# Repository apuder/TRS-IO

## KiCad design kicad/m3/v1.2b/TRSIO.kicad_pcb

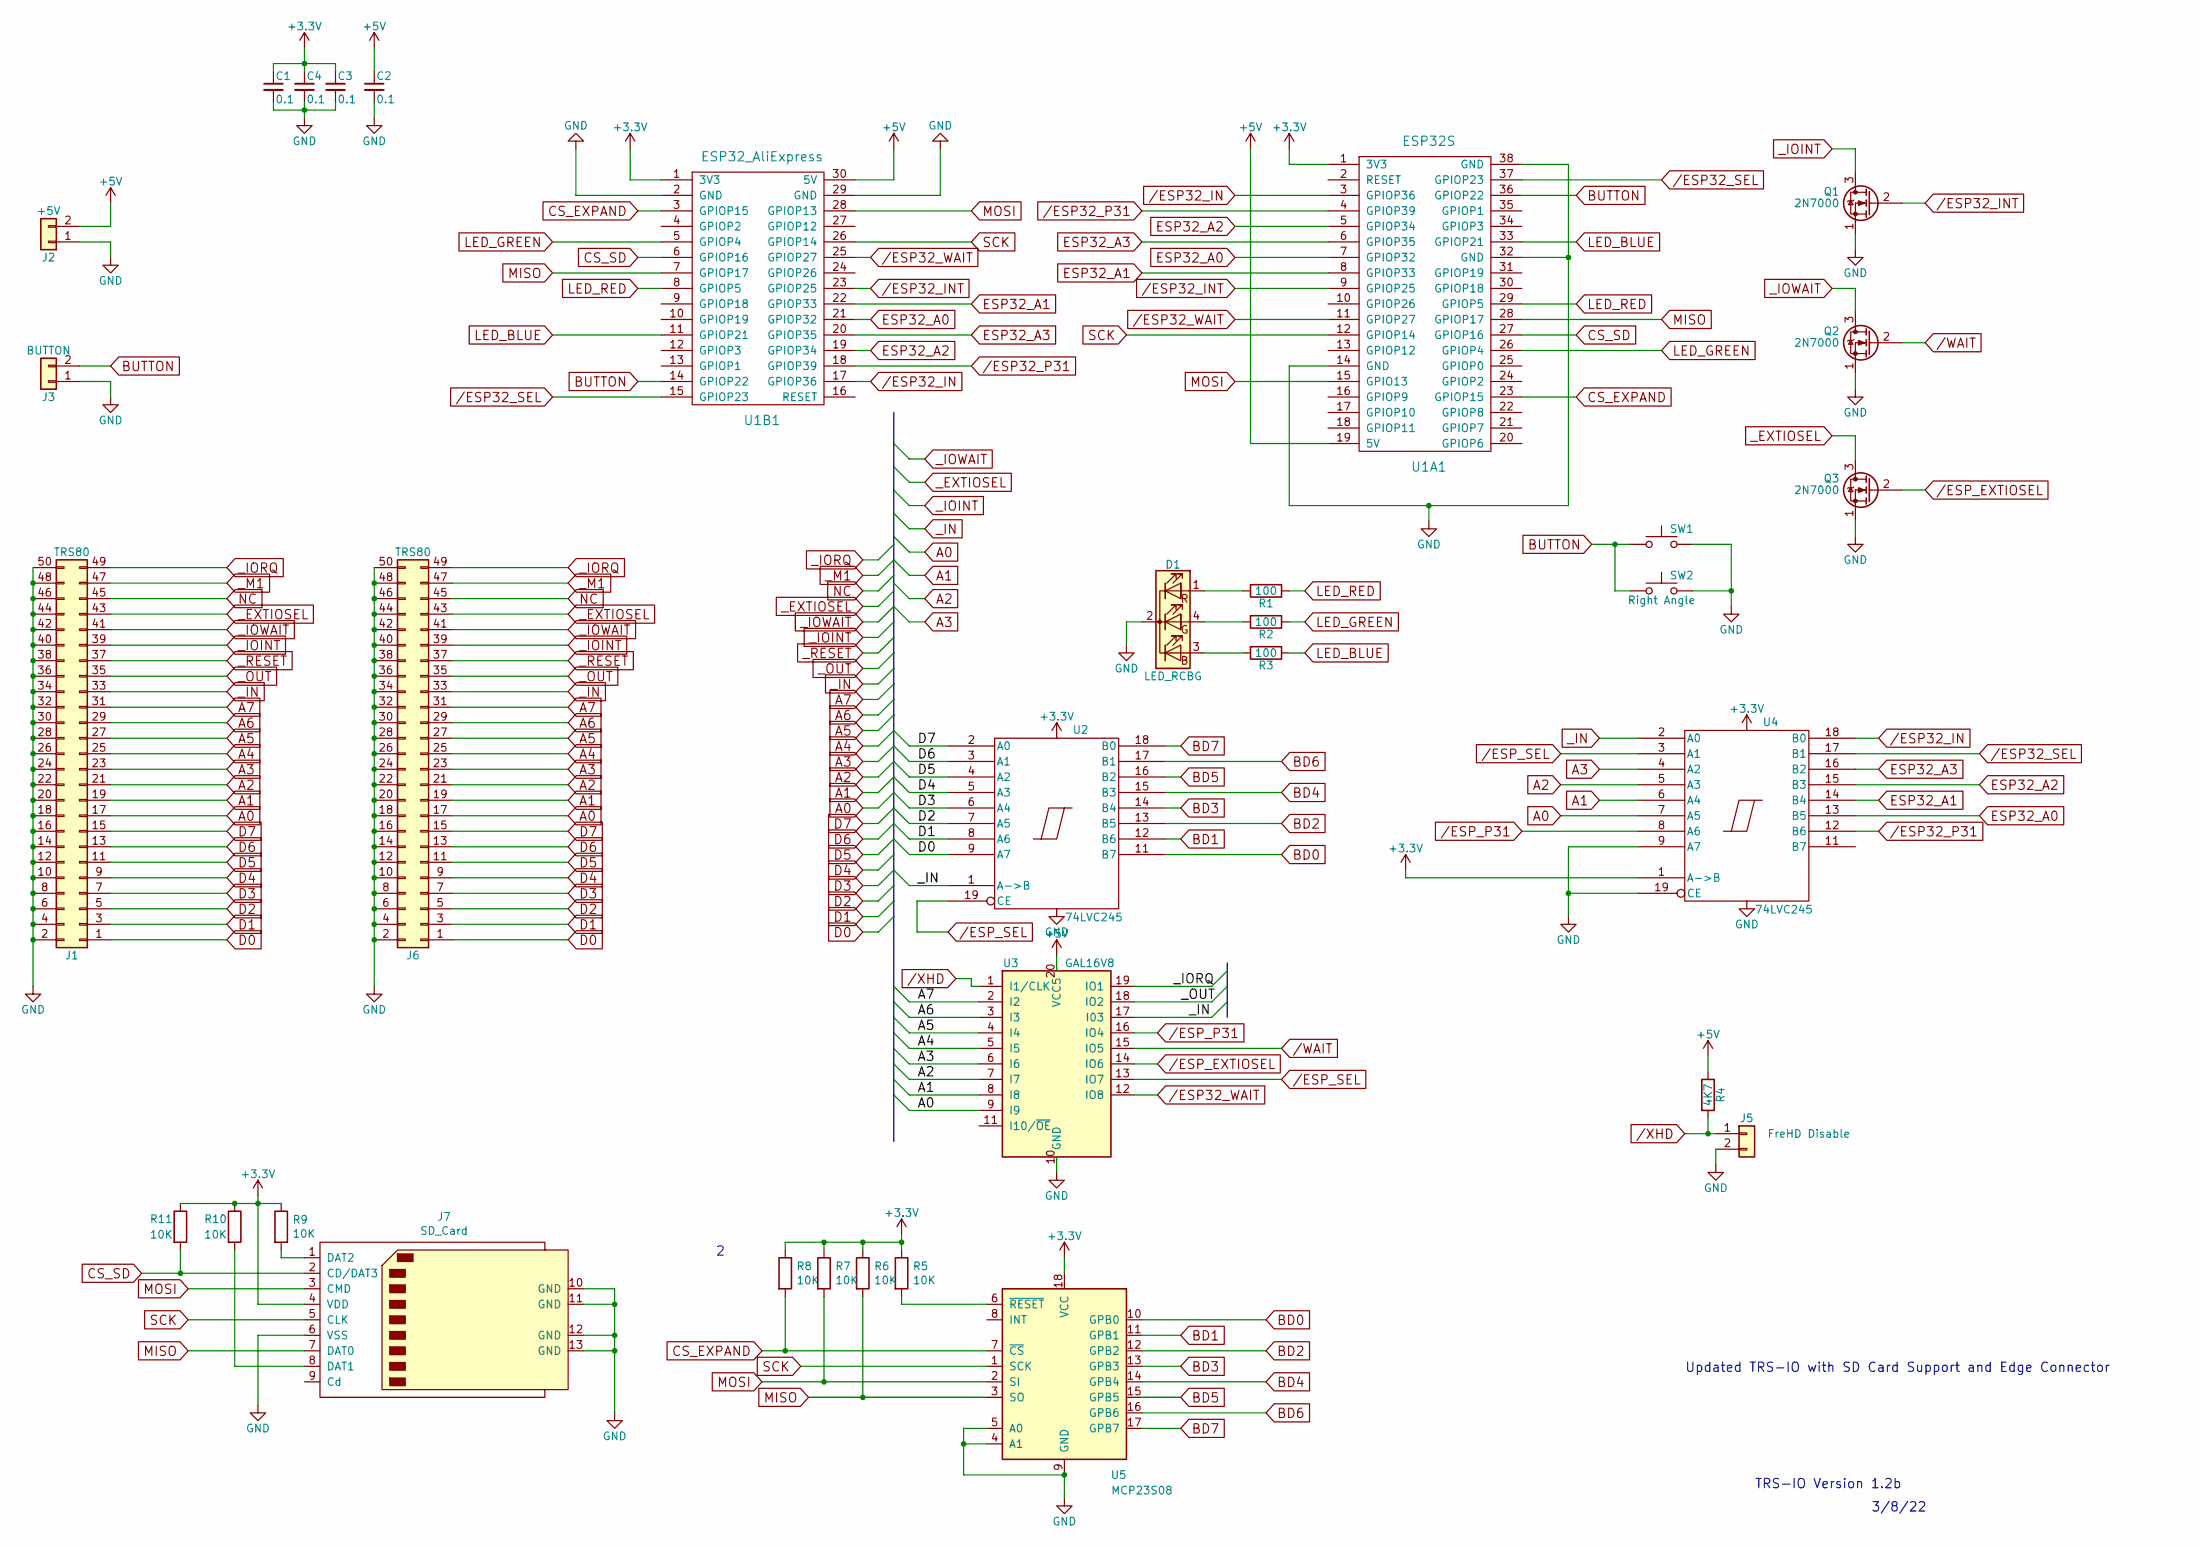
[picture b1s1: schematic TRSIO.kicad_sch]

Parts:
C1, C2, C3, C4: 0.1; C_Disc_D3.0mm_W2.0mm_P2.50mm
D1: LED_RCBG; LED_D5.0mm-4
J1: TRS80; Pin_Header_Straight_2x25_Pitch2.54mm
J2: +5V; Pin_Header_Straight_1x02_Pitch2.54mm
J3: BUTTON; Pin_Header_Straight_1x02_Pitch2.54mm
J5: FreHD Disable; Pin_Header_Straight_1x02_Pitch2.54mm
J6: TRS80; EDGE50
J7: SD_Card; TFP09-2-12B
Q1, Q2, Q3: 2N7000; TO-92_Molded_Narrow
R1, R2, R3: 100; R_Axial_DIN0207_L6.3mm_D2.5mm_P7.62mm_Horizontal
R4: 4K7; R_Axial_DIN0207_L6.3mm_D2.5mm_P7.62mm_Horizontal
R5, R6, R7, R8, R9, R10, R11: 10K; R_Axial_DIN0207_L6.3mm_D2.5mm_P7.62mm_Horizontal
SW1: SW_Push; SW_PUSH_6mm_h9.5mm
SW2: Right Angle; SW_Tactile_SPST_Angled_PTS645Vx31-2LFS
U1A1: ESP32S; DIP-38_W22.9mm
U1B1: ESP32_AliExpress; DIP-30_W25.4mm
U2, U4: 74LVC245; DIP-20_W7.62mm
U3: GAL16V8; DIP-20_W7.62mm
U5: MCP23S08; DIP-18_W7.62mm

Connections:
+3V3: C1.1, C3.1, C4.1, J7.4 (VDD), R5.1, R6.1, R7.1, R8.1, R9.1, R10.1, R11.1, U1A1.1 (3V3), U1B1.1 (3V3), U2.20 (VCC), U4.1 (A->B), U4.20 (VCC), U5.18 (VCC)
+5V: C2.1, J2.2, R4.1, U1A1.19 (5V), U1B1.30 (5V), U3.20 (VCC5)
A0: J1.17, J6.17, U3.9 (I9), U4.7 (A5)
A1: J1.19, J6.19, U3.8 (I8), U4.6 (A4)
A2: J1.21, J6.21, U3.7 (I7), U4.5 (A3)
A3: J1.23, J6.23, U3.6 (I6), U4.4 (A2)
A4: J1.25, J6.25, U3.5 (I5)
A5: J1.27, J6.27, U3.4 (I4)
A6: J1.29, J6.29, U3.3 (I3)
A7: J1.31, J6.31, U3.2 (I2)
BD0: U2.11 (B7), U5.10 (GPB0)
BD1: U2.12 (B6), U5.11 (GPB1)
BD2: U2.13 (B5), U5.12 (GPB2)
BD3: U2.14 (B4), U5.13 (GPB3)
BD4: U2.15 (B3), U5.14 (GPB4)
BD5: U2.16 (B2), U5.15 (GPB5)
BD6: U2.17 (B1), U5.16 (GPB6)
BD7: U2.18 (B0), U5.17 (GPB7)
BUTTON: J3.2, SW1.1, SW2.1, U1A1.36 (GPIOP22), U1B1.14 (GPIOP22)
CS_EXPAND: R8.2, U1A1.23 (GPIOP15), U1B1.3 (GPIOP15), U5.7 (~CS)
CS_SD: J7.2 (CD/DAT3), R11.2, U1A1.27 (GPIOP16), U1B1.6 (GPIOP16)
D0: J1.1, J6.1, U2.9 (A7)
D1: J1.3, J6.3, U2.8 (A6)
D2: J1.5, J6.5, U2.7 (A5)
D3: J1.7, J6.7, U2.6 (A4)
D4: J1.9, J6.9, U2.5 (A3)
D5: J1.11, J6.11, U2.4 (A2)
D6: J1.13, J6.13, U2.3 (A1)
D7: J1.15, J6.15, U2.2 (A0)
ESP32_A0: U1A1.7 (GPIOP32), U1B1.21 (GPIOP32), U4.13 (B5)
ESP32_A1: U1A1.8 (GPIOP33), U1B1.22 (GPIOP33), U4.14 (B4)
ESP32_A2: U1A1.5 (GPIOP34), U1B1.19 (GPIOP34), U4.15 (B3)
ESP32_A3: U1A1.6 (GPIOP35), U1B1.20 (GPIOP35), U4.16 (B2)
GND: C1.2, C2.2, C3.2, C4.2, D1.2 (K), J1.2, J1.4, J1.6, J1.8, J1.10, J1.12, J1.14, J1.16, J1.18, J1.20, J1.22, J1.24, J1.26, J1.28, J1.30, J1.32, J1.34, J1.36, J1.38, J1.40, J1.42, J1.44, J1.46, J1.48, J1.50, J2.1, J3.1, J5.2, J6.2, J6.4, J6.6, J6.8, J6.10, J6.12, J6.14, J6.16, J6.18, J6.20, J6.22, J6.24, J6.26, J6.28, J6.30, J6.32, J6.34, J6.36, J6.38, J6.40, J6.42, J6.44, J6.46, J6.48, J6.50, J7.6 (VSS), J7.10 (GND), J7.11 (GND), J7.12 (GND), J7.13 (GND), Q1.1 (S), Q2.1 (S), Q3.1 (S), SW1.2, SW2.2, U1A1.14 (GND), U1A1.32 (GND), U1A1.38 (GND), U1B1.2 (GND), U1B1.29 (GND), U2.10 (GND), U3.10 (GND), U4.9 (A7), U4.10 (GND), U4.19 (CE), U5.4 (A1), U5.5 (A0), U5.9 (GND)
LED_BLUE: R3.1, U1A1.33 (GPIOP21), U1B1.11 (GPIOP21)
LED_GREEN: R2.1, U1A1.26 (GPIOP4), U1B1.5 (GPIOP4)
LED_RED: R1.1, U1A1.29 (GPIOP5), U1B1.8 (GPIOP5)
MISO: J7.7 (DAT0), R6.2, U1A1.28 (GPIOP17), U1B1.7 (GPIOP17), U5.3 (SO)
MOSI: J7.3 (CMD), R7.2, U1A1.15 (GPIO13), U1B1.28 (GPIOP13), U5.2 (SI)
NC: J1.45, J6.45
unnamed: D1.1 (RA), R1.2
unnamed: D1.3 (BA), R3.2
unnamed: D1.4 (GA), R2.2
unnamed: J7.1 (DAT2), R9.2
unnamed: J7.8 (DAT1), R10.2
unnamed: R5.2, U5.6 (~RESET)
SCK: J7.5 (CLK), U1A1.12 (GPIOP14), U1B1.26 (GPIOP14), U5.1 (SCK)
_EXTIOSEL: J1.43, J6.43, Q3.3 (D)
_IN: J1.33, J6.33, U2.1 (A->B), U3.17 (I03), U4.2 (A0)
_IOINT: J1.39, J6.39, Q1.3 (D)
_IORQ: J1.49, J6.49, U3.19 (IO1)
_IOWAIT: J1.41, J6.41, Q2.3 (D)
_M1: J1.47, J6.47
_OUT: J1.35, J6.35, U3.18 (IO2)
_RESET: J1.37, J6.37
/ESP32_IN: U1A1.3 (GPIOP36), U1B1.17 (GPIOP36), U4.18 (B0)
/ESP32_INT: Q1.2 (G), U1A1.9 (GPIOP25), U1B1.23 (GPIOP25)
/ESP32_P31: U1A1.4 (GPIOP39), U1B1.18 (GPIOP39), U4.12 (B6)
/ESP32_SEL: U1A1.37 (GPIOP23), U1B1.15 (GPIOP23), U4.17 (B1)
/ESP32_WAIT: U1A1.11 (GPIOP27), U1B1.25 (GPIOP27), U3.12 (IO8)
/ESP_EXTIOSEL: Q3.2 (G), U3.14 (IO6)
/ESP_P31: U3.16 (IO4), U4.8 (A6)
/ESP_SEL: U2.19 (CE), U3.13 (IO7), U4.3 (A1)
/WAIT: Q2.2 (G), U3.15 (IO5)
/XHD: J5.1, R4.2, U3.1 (I1/CLK)

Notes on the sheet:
TRS-IO Version 1.2b
Updated TRS-IO with SD Card Support and Edge Connector
3/8/22

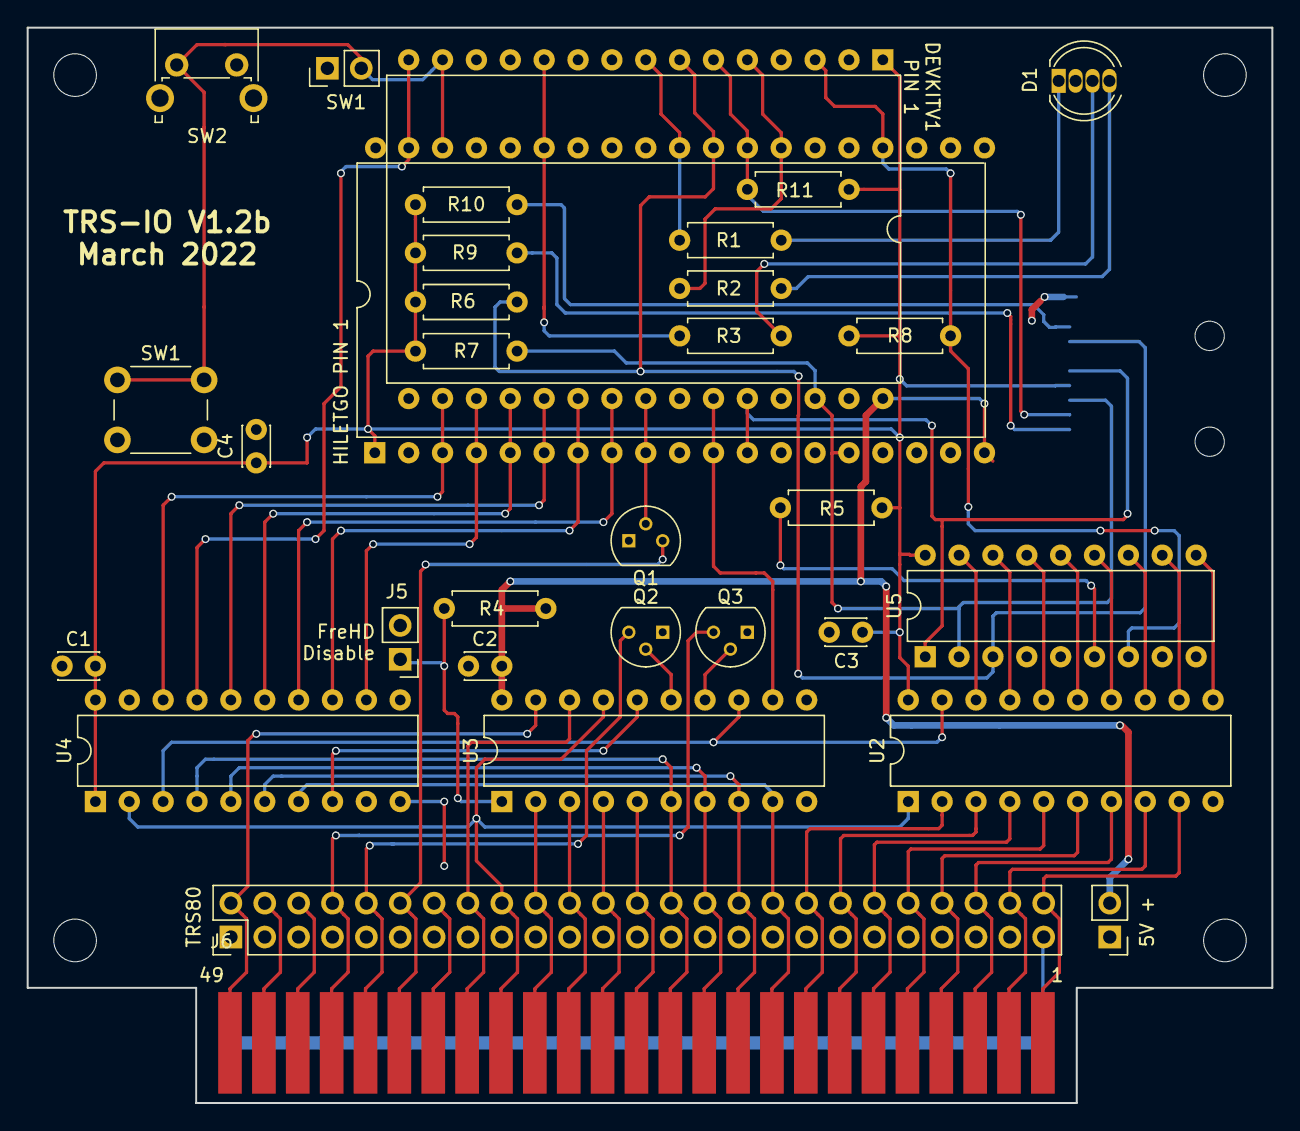
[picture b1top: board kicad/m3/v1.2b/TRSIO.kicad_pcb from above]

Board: 2 copper layers, 93.3 x 80.6 mm, 33 parts (1 on the bottom side), 65 nets.

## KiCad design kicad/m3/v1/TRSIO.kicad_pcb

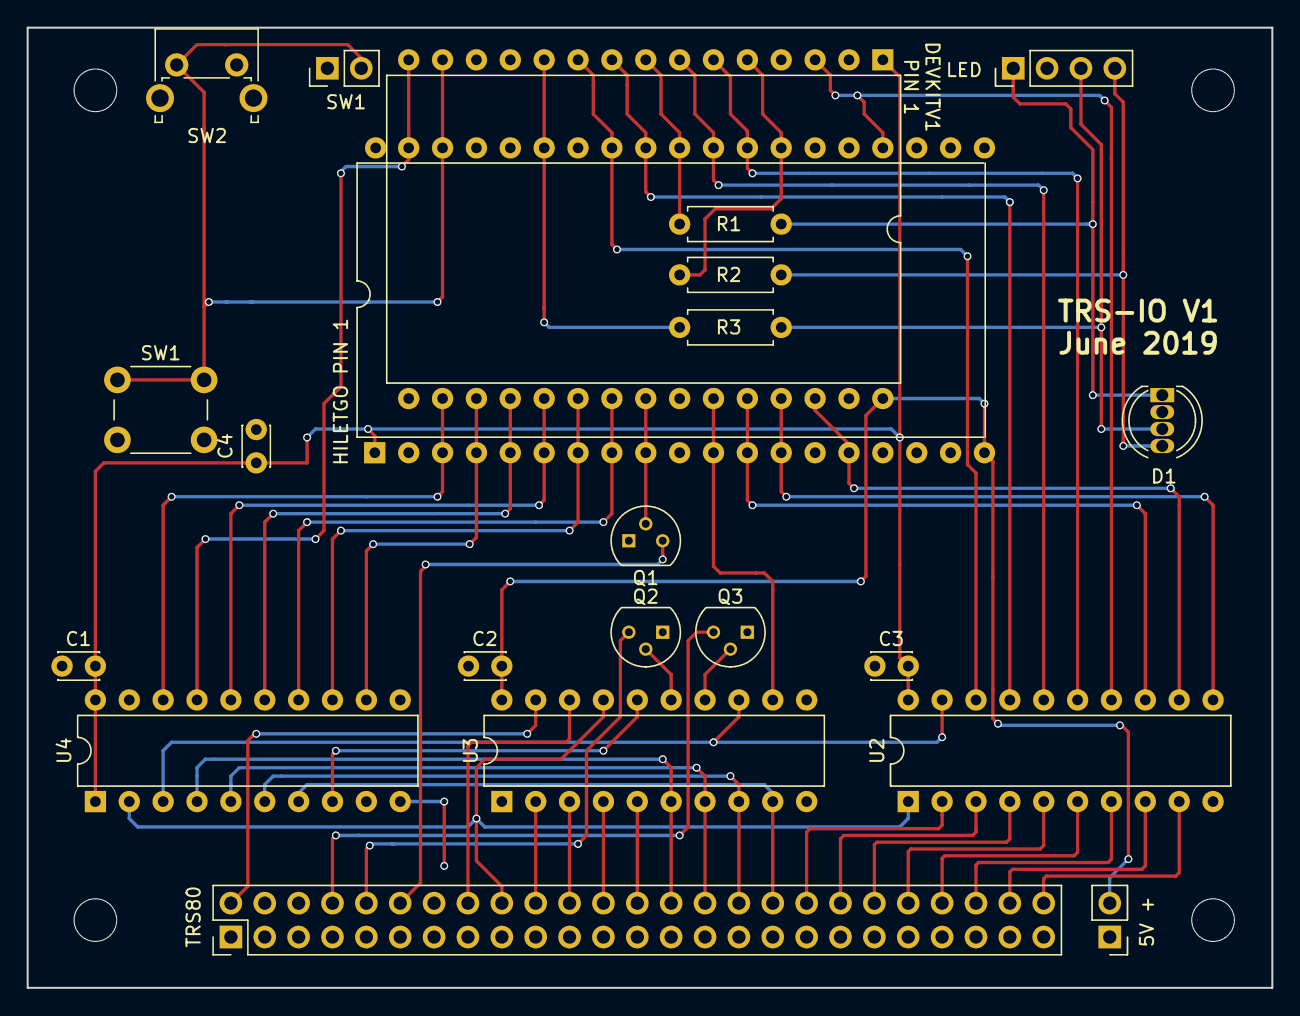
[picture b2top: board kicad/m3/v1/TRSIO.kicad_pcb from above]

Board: 2 copper layers, 93.3 x 72.0 mm, 22 parts (0 on the bottom side), 53 nets.

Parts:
C1, C2, C3, C4: 0.1; C_Disc_D3.0mm_W2.0mm_P2.50mm
D1: LED_RCBG; LED_D5.0mm-4
J1: TRS80; Pin_Header_Straight_2x25_Pitch2.54mm
J2: +5V; Pin_Header_Straight_1x02_Pitch2.54mm
J3: BUTTON; Pin_Header_Straight_1x02_Pitch2.54mm
J4: LED; Pin_Header_Straight_1x04_Pitch2.54mm
Q1, Q2, Q3: 2N7000; TO-92_Molded_Narrow
R1, R2, R3: 100; R_Axial_DIN0207_L6.3mm_D2.5mm_P7.62mm_Horizontal
SW1: SW_Push; SW_PUSH_6mm_h9.5mm
SW2: Right Angle; SW_Tactile_SPST_Angled_PTS645Vx31-2LFS
U1A1: ESP32S; DIP-38_W22.9mm
U1B1: ESP32_AliExpress; DIP-30_W25.4mm
U2, U4: 74LVC245; DIP-20_W7.62mm
U3: GAL16V8; DIP-20_W7.62mm

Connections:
+3V3: C1.1, C3.1, C4.1, U1A1.1, U1B1.1, U2.20, U4.1, U4.20
+5V: C2.1, J2.2, U1A1.19, U1B1.30, U3.20
//IORQ: J1.49, U3.19
//OUT: J1.35, U3.18
/A4: J1.25, U3.5
/A5: J1.27, U3.4
/A6: J1.29, U3.3
/A7: J1.31, U3.2
/D0: J1.1, U2.9
/D1: J1.3, U2.8
/D2: J1.5, U2.7
/D3: J1.7, U2.6
/D4: J1.9, U2.5
/D5: J1.11, U2.4
/D6: J1.13, U2.3
/D7: J1.15, U2.2
/ESP32_IN: U1A1.3, U1B1.17, U4.18
/ESP32_INT: Q1.2, U1A1.9, U1B1.23
/ESP32_P31: U1A1.4, U1B1.18, U4.12
/ESP32_SEL: U1A1.37, U1B1.15, U4.17
/ESP32_WAIT: U1A1.11, U1B1.25, U3.12
/ESP_EXTIOSEL: Q3.2, U3.14
/ESP_P31: U3.16, U4.8
/ESP_SEL: U2.19, U3.13, U4.3
/EXTIOSEL: J1.43, Q3.3
/IN: J1.33, U2.1, U3.17, U4.2
/IOINT: J1.39, Q1.3
/IOWAIT: J1.41, Q2.3
/WAIT: Q2.2, U3.15
A0: J1.17, U3.9, U4.7
A1: J1.19, U3.8, U4.6
A2: J1.21, U3.7, U4.5
A3: J1.23, U3.6, U4.4
BUTTON: J3.2, SW1.1, SW2.1, U1A1.36, U1B1.14
ESP32_A0: U1A1.7, U1B1.21, U4.13
ESP32_A1: U1A1.8, U1B1.22, U4.14
ESP32_A2: U1A1.5, U1B1.19, U4.15
ESP32_A3: U1A1.6, U1B1.20, U4.16
ESP32_D0: U1A1.13, U1B1.27, U2.11
ESP32_D1: U1A1.15, U1B1.28, U2.12
ESP32_D2: U1A1.12, U1B1.26, U2.13
ESP32_D3: U1A1.23, U1B1.3, U2.14
ESP32_D4: U1A1.27, U1B1.6, U2.15
ESP32_D5: U1A1.28, U1B1.7, U2.16
ESP32_D6: U1A1.30, U1B1.9, U2.17
ESP32_D7: U1A1.31, U1B1.10, U2.18
EXT_BLUE: D1.3, J4.3, R3.2
EXT_GREEN: D1.4, J4.4, R2.2
EXT_RED: D1.1, J4.1, R1.2
GND: C1.2, C2.2, C3.2, C4.2, D1.2, J1.2, J1.4, J1.6, J1.8, J1.10, J1.12, J1.14, J1.16, J1.18, J1.20, J1.22, J1.24, J1.26, J1.28, J1.30, J1.32, J1.34, J1.36, J1.38, J1.40, J1.42, J1.44, J1.46, J1.48, J1.50, J2.1, J3.1, J4.2, Q1.1, Q2.1, Q3.1, SW1.2, SW2.2, U1A1.14, U1A1.32, U1A1.38, U1B1.2, U1B1.29, U2.10, U3.10, U4.9, U4.10, U4.19
LED_BLUE: R3.1, U1A1.33, U1B1.11
LED_GREEN: R2.1, U1A1.26, U1B1.5
LED_RED: R1.1, U1A1.29, U1B1.8

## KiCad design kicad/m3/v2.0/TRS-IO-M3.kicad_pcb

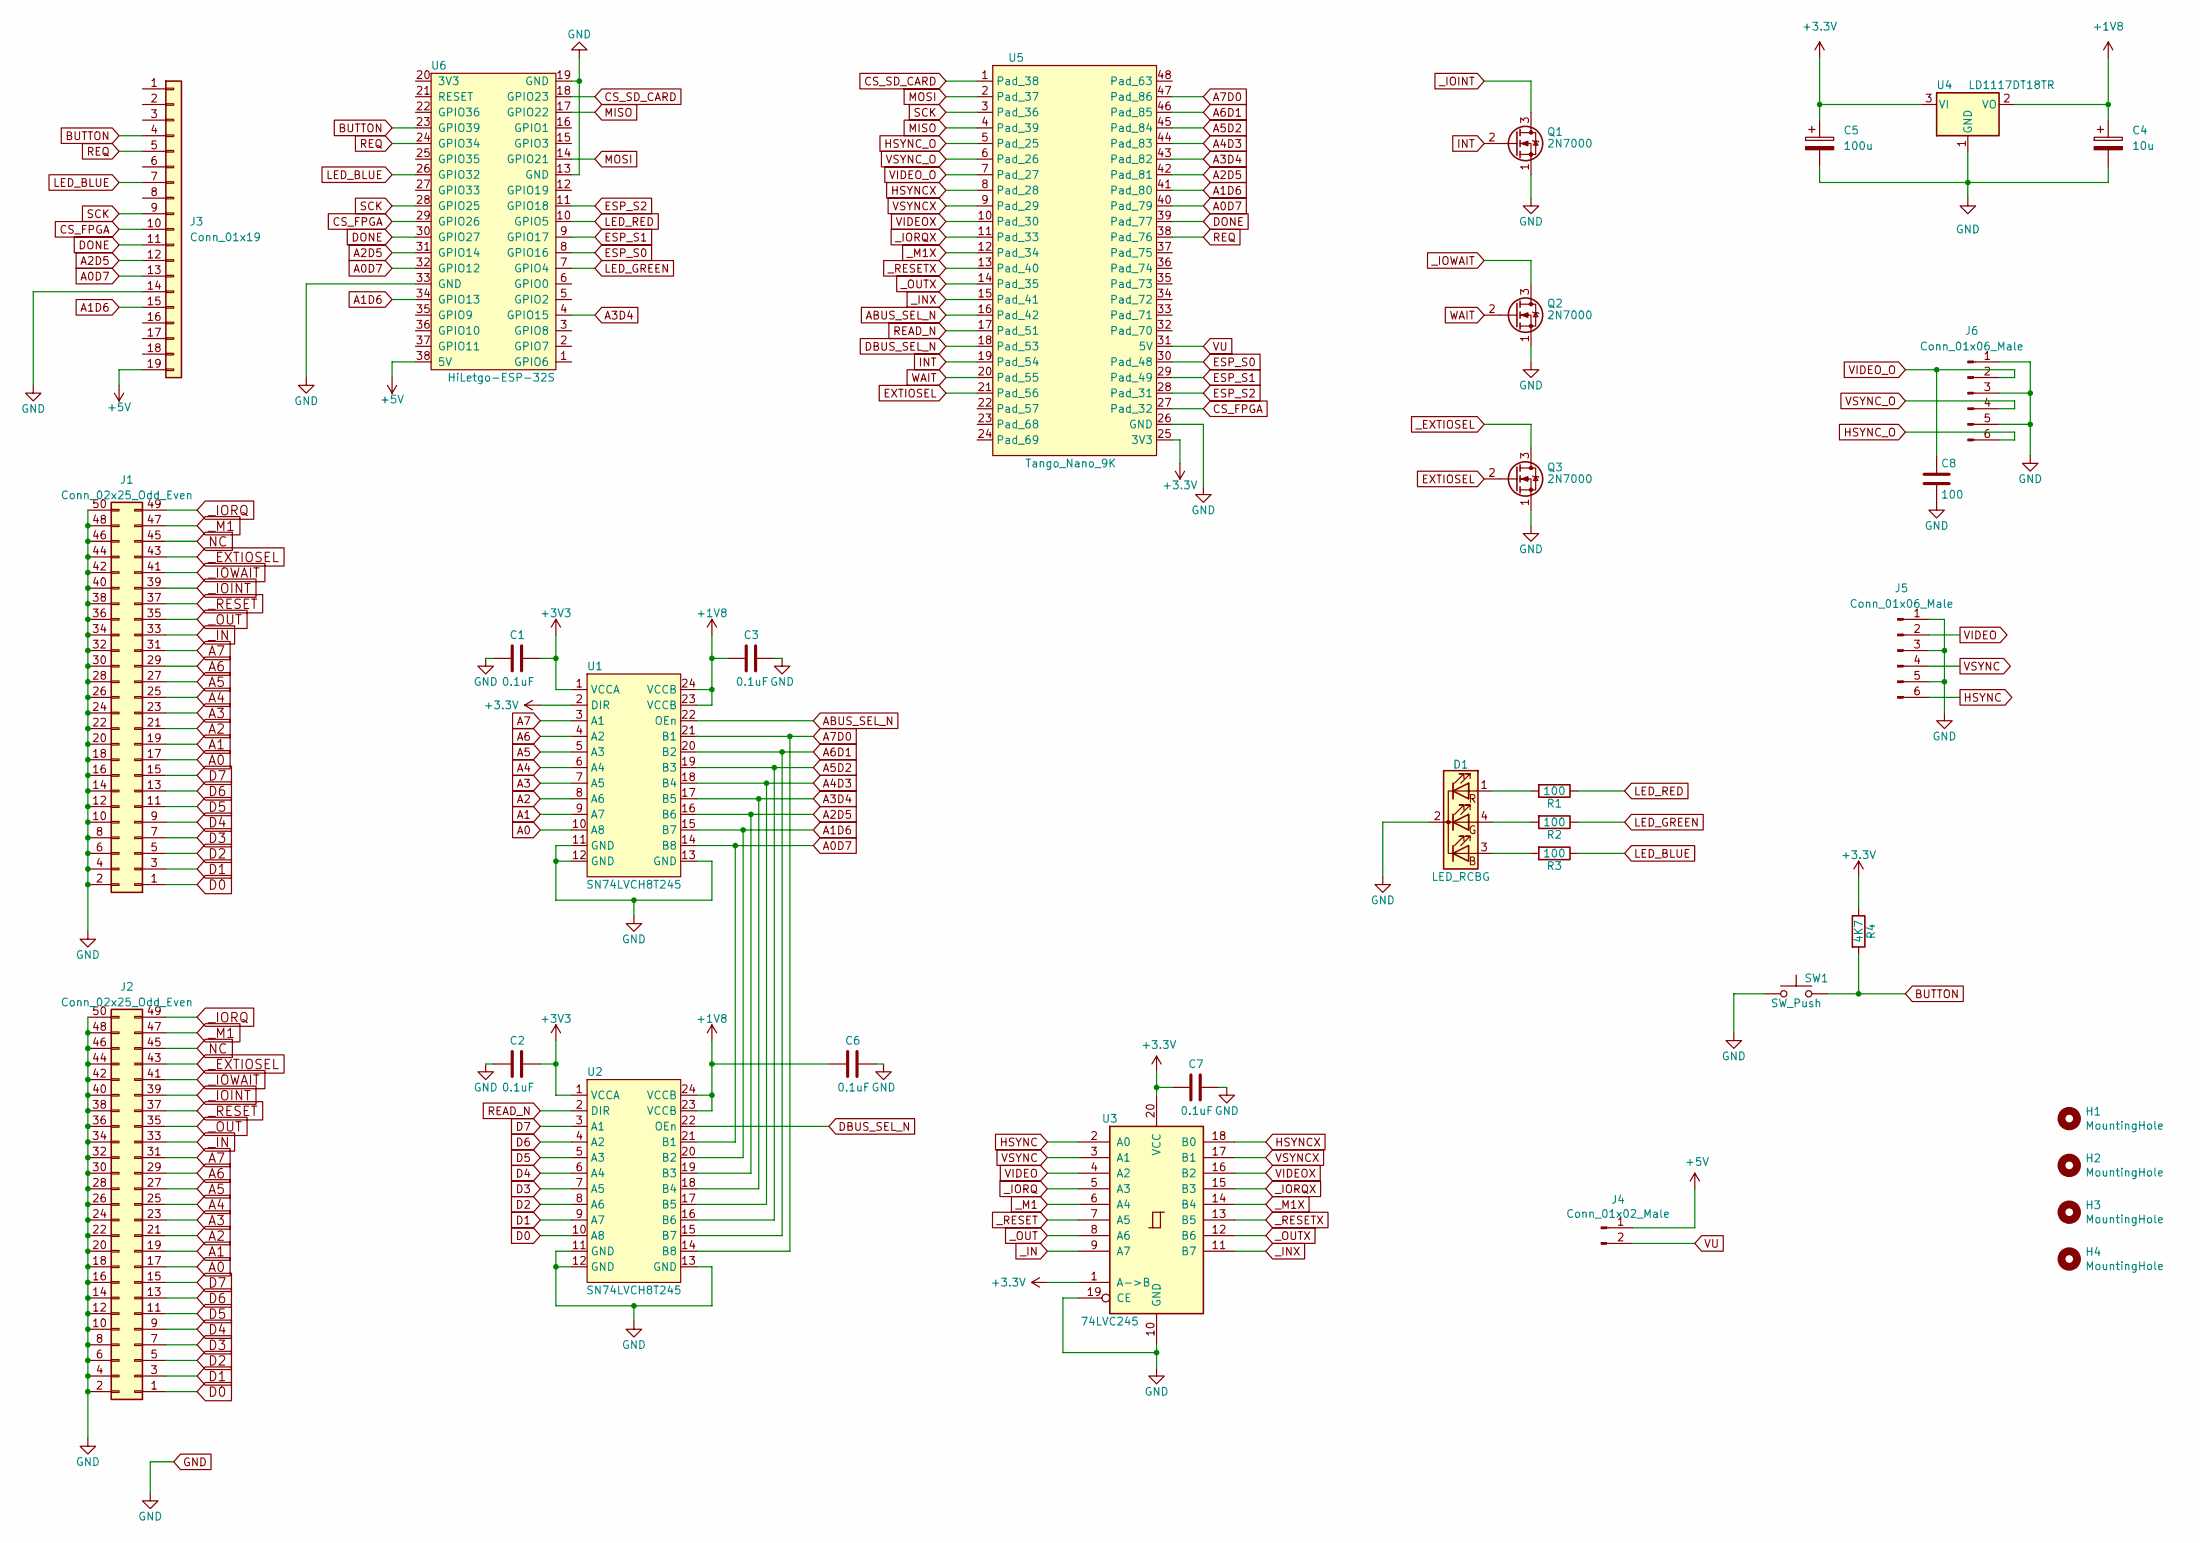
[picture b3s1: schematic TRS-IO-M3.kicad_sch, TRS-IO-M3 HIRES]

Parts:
C1, C2, C3, C6, C7: 0.1uF; C_0805_2012Metric_Pad1.18x1.45mm_HandSolder
C4: 10u; C_1206_3216Metric_Pad1.33x1.80mm_HandSolder
C5: 100u; C_1206_3216Metric_Pad1.33x1.80mm_HandSolder
C8: 100; C_0805_2012Metric_Pad1.18x1.45mm_HandSolder
D1: LED_RCBG; LED_D5.0mm-4_RGB
H1, H2, H3, H4: MountingHole; MountingHole_3mm_Pad_Via
J1: Conn_02x25_Odd_Even; EDGE50
J2: Conn_02x25_Odd_Even; Pin_Header_Straight_2x25_Pitch2.54mm
J3: Conn_01x19; PinHeader_1x19_P2.54mm_Vertical
J4: Conn_01x02_Male; PinHeader_1x02_P2.54mm_Vertical
J5, J6: Conn_01x06_Male; PinHeader_1x06_P2.54mm_Horizontal
Q1, Q2, Q3: 2N7000; TO-92_Inline
R1, R2, R3: 100; R_Axial_DIN0207_L6.3mm_D2.5mm_P7.62mm_Horizontal
R4: 4K7; R_Axial_DIN0207_L6.3mm_D2.5mm_P7.62mm_Horizontal
SW1: SW_Push; SW_PUSH_6mm_H9.5mm
U1, U2: SN74LVCH8T245; TSSOP-24_4.4x7.8mm_P0.65mm
U3: 74LVC245; SSOP-20_5.3x7.2mm_P0.65mm
U4: LD1117DT18TR; TO-252-3_TabPin2
U5: Tango_Nano_9K; DIP-48_W22.9mm
U6: HiLetgo-ESP-32S; DIP-38_W22.9mm

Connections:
+1V8: C3.2, C4.1, C6.2, U1.23 (VCCB), U1.24 (VCCB), U2.23 (VCCB), U2.24 (VCCB), U4.2 (VO)
+5V: J3.19, J4.1, U6.38 (5V)
A0: J1.17, J2.17, U1.10 (A8)
A0D7: J3.13, U1.14 (B8), U2.21 (B1), U5.40 (Pad_79), U6.32 (GPIO12)
A1: J1.19, J2.19, U1.9 (A7)
A1D6: J3.15, U1.15 (B7), U2.20 (B2), U5.41 (Pad_80), U6.34 (GPIO13)
A2: J1.21, J2.21, U1.8 (A6)
A2D5: J3.12, U1.16 (B6), U2.19 (B3), U5.42 (Pad_81), U6.31 (GPIO14)
A3: J1.23, J2.23, U1.7 (A5)
A3D4: U1.17 (B5), U2.18 (B4), U5.43 (Pad_82), U6.4 (GPIO15)
A4: J1.25, J2.25, U1.6 (A4)
A4D3: U1.18 (B4), U2.17 (B5), U5.44 (Pad_83)
A5: J1.27, J2.27, U1.5 (A3)
A5D2: U1.19 (B3), U2.16 (B6), U5.45 (Pad_84)
A6: J1.29, J2.29, U1.4 (A2)
A6D1: U1.20 (B2), U2.15 (B7), U5.46 (Pad_85)
A7: J1.31, J2.31, U1.3 (A1)
A7D0: U1.21 (B1), U2.14 (B8), U5.47 (Pad_86)
ABUS_SEL_N: U1.22 (OEn), U5.16 (Pad_42)
BUTTON: J3.4, R4.2, SW1.2, U6.23 (GPIO39)
CS_FPGA: J3.10, U5.27 (Pad_32), U6.29 (GPIO26)
CS_SD_CARD: U5.1 (Pad_38), U6.18 (GPIO23)
D0: J1.1, J2.1, U2.10 (A8)
D1: J1.3, J2.3, U2.9 (A7)
D2: J1.5, J2.5, U2.8 (A6)
D3: J1.7, J2.7, U2.7 (A5)
D4: J1.9, J2.9, U2.6 (A4)
D5: J1.11, J2.11, U2.5 (A3)
D6: J1.13, J2.13, U2.4 (A2)
D7: J1.15, J2.15, U2.3 (A1)
DBUS_SEL_N: U2.22 (OEn), U5.18 (Pad_53)
DONE: J3.11, U5.39 (Pad_77), U6.30 (GPIO27)
ESP_S0: U5.30 (Pad_48), U6.8 (GPIO16)
ESP_S1: U5.29 (Pad_49), U6.9 (GPIO17)
ESP_S2: U5.28 (Pad_31), U6.11 (GPIO18)
EXTIOSEL: Q3.2 (G), U5.21 (Pad_56)
GND: C1.2, C2.2, C3.1, C4.2, C5.2, C6.1, C7.1, C8.2, D1.2 (K), J1.2, J1.4, J1.6, J1.8, J1.10, J1.12, J1.14, J1.16, J1.18, J1.20, J1.22, J1.24, J1.26, J1.28, J1.30, J1.32, J1.34, J1.36, J1.38, J1.40, J1.42, J1.44, J1.46, J1.48, J1.50, J2.2, J2.4, J2.6, J2.8, J2.10, J2.12, J2.14, J2.16, J2.18, J2.20, J2.22, J2.24, J2.26, J2.28, J2.30, J2.32, J2.34, J2.36, J2.38, J2.40, J2.42, J2.44, J2.46, J2.48, J2.50, J3.14, J5.1, J5.3, J5.5, J6.1, J6.3, J6.5, Q1.1 (S), Q2.1 (S), Q3.1 (S), SW1.1, U1.11 (GND), U1.12 (GND), U1.13 (GND), U2.11 (GND), U2.12 (GND), U2.13 (GND), U3.10 (GND), U3.19 (CE), U4.1 (GND), U5.26 (GND), U6.13 (GND), U6.19 (GND), U6.33 (GND)
HSYNC: J5.6, U3.2 (A0)
HSYNCX: U3.18 (B0), U5.8 (Pad_28)
HSYNC_O: J6.6, U5.5 (Pad_25)
INT: Q1.2 (G), U5.19 (Pad_54)
LED_BLUE: J3.7, R3.1, U6.26 (GPIO32)
LED_GREEN: R2.1, U6.7 (GPIO4)
LED_RED: R1.1, U6.10 (GPIO5)
MISO: U5.4 (Pad_39), U6.17 (GPIO22)
MOSI: U5.2 (Pad_37), U6.14 (GPIO21)
NC: J1.45, J2.45
unnamed: D1.1 (RA), R1.2
unnamed: D1.3 (BA), R3.2
unnamed: D1.4 (GA), R2.2
READ_N: U2.2 (DIR), U5.17 (Pad_51)
REQ: J3.5, U5.38 (Pad_76), U6.24 (GPIO34)
SCK: J3.9, U5.3 (Pad_36), U6.28 (GPIO25)
VIDEO: J5.2, U3.4 (A2)
VIDEOX: U3.16 (B2), U5.10 (Pad_30)
VIDEO_O: C8.1, J6.2, U5.7 (Pad_27)
VSYNC: J5.4, U3.3 (A1)
VSYNCX: U3.17 (B1), U5.9 (Pad_29)
VSYNC_O: J6.4, U5.6 (Pad_26)
VU: J4.2, U5.31 (5V)
WAIT: Q2.2 (G), U5.20 (Pad_55)
_EXTIOSEL: J1.43, J2.43, Q3.3 (D)
_IN: J1.33, J2.33, U3.9 (A7)
_INX: U3.11 (B7), U5.15 (Pad_41)
_IOINT: J1.39, J2.39, Q1.3 (D)
_IORQ: J1.49, J2.49, U3.5 (A3)
_IORQX: U3.15 (B3), U5.11 (Pad_33)
_IOWAIT: J1.41, J2.41, Q2.3 (D)
_M1: J1.47, J2.47, U3.6 (A4)
_M1X: U3.14 (B4), U5.12 (Pad_34)
_OUT: J1.35, J2.35, U3.8 (A6)
_OUTX: U3.12 (B6), U5.14 (Pad_35)
_RESET: J1.37, J2.37, U3.7 (A5)
_RESETX: U3.13 (B5), U5.13 (Pad_40)

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
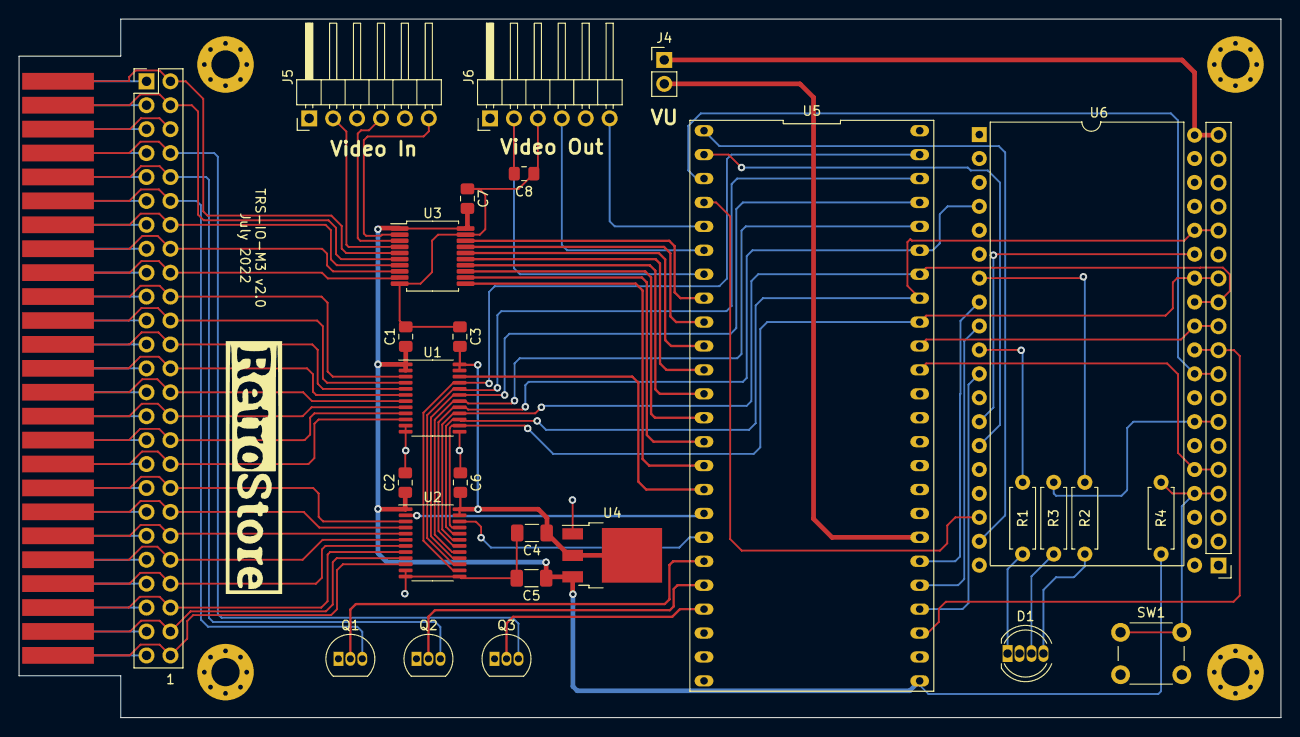
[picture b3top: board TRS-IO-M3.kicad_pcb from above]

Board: 2 copper layers, 134.0 x 74.2 mm, 34 parts (0 on the bottom side), 75 nets.

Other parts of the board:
G1: LOGO
